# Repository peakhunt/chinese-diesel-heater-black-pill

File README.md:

# chinese-diesel-heater-black-pill
stm32f4 based chinese diesel heater

# again Dangerous!
I'm not interested in adding any safety features as of now!

# a little documentation
to be done

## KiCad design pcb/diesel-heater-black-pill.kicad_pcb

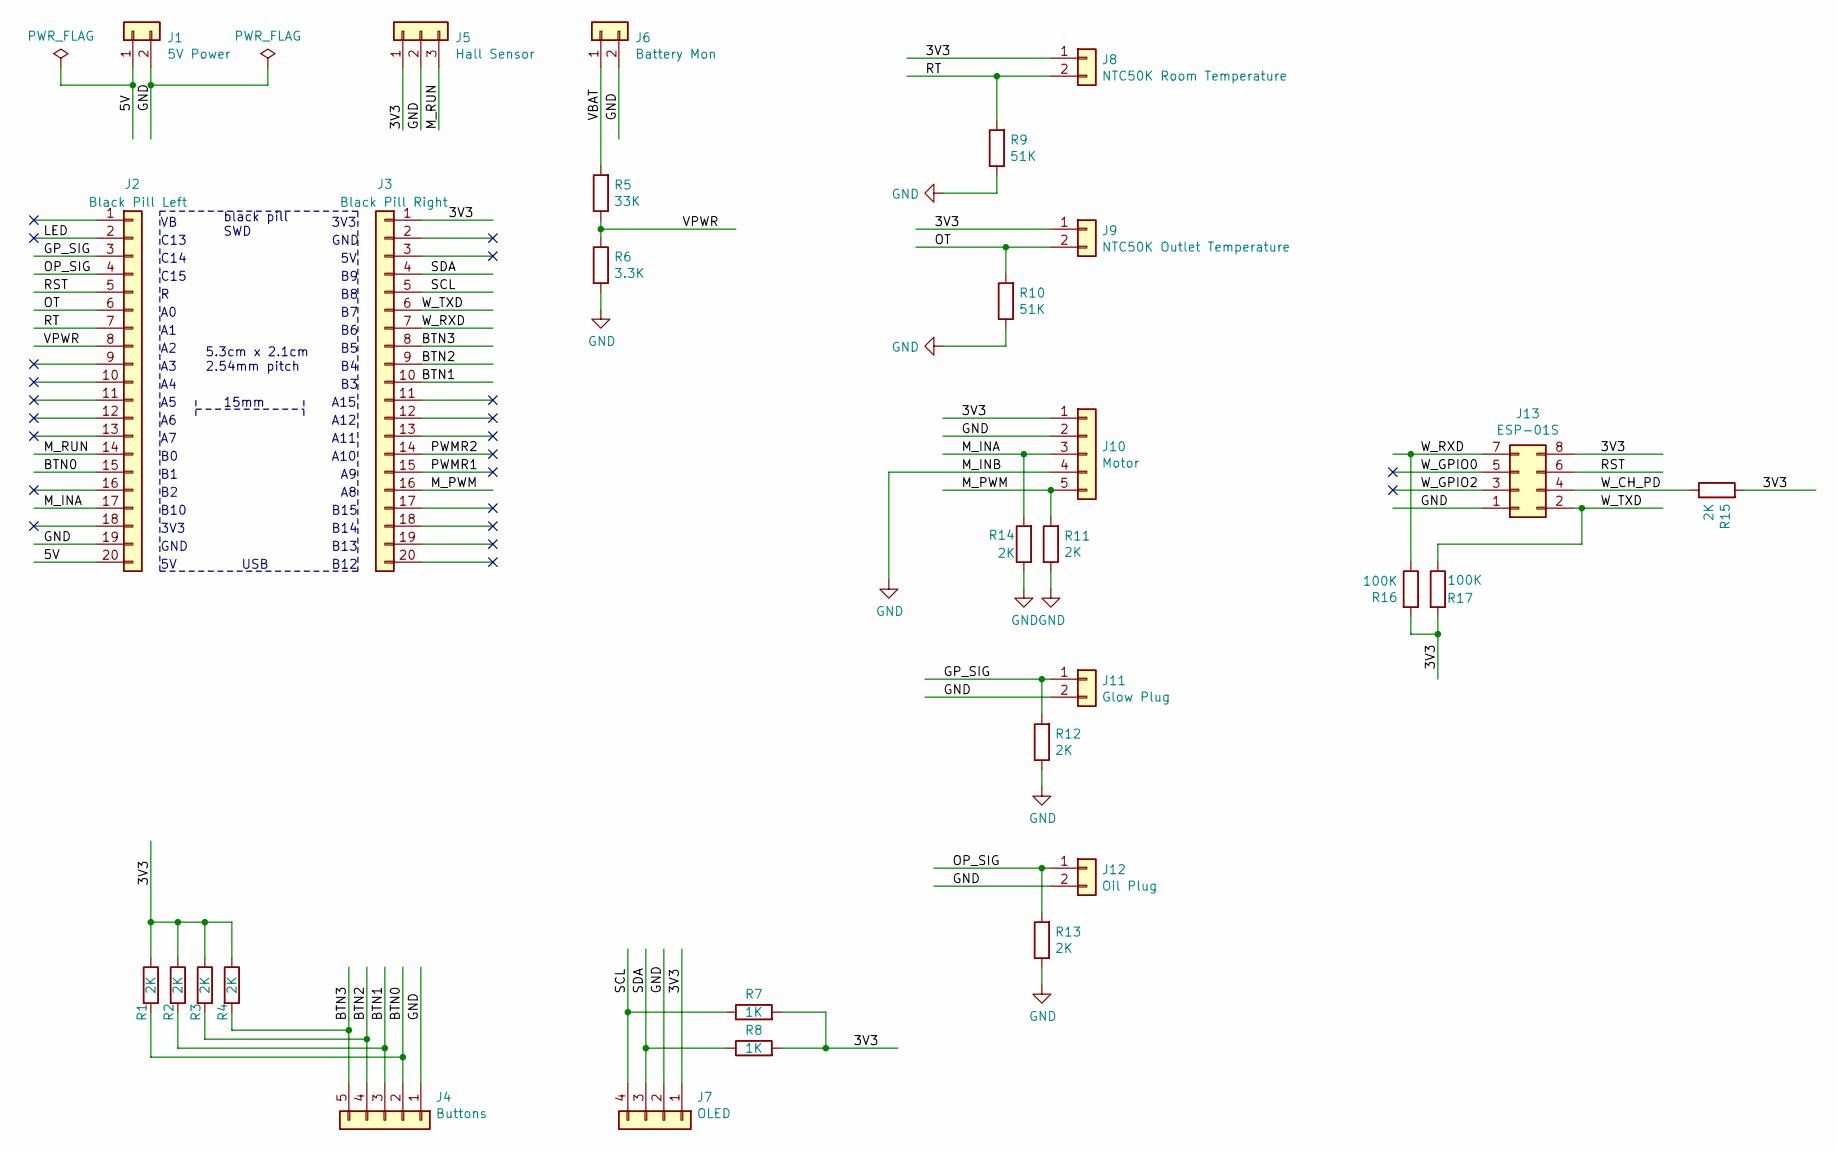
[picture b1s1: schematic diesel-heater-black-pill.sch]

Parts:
J1: 5V Power; JST_XH_B2B-XH-A_1x02_P2.50mm_Vertical
J2: Black Pill Left; PinSocket_1x20_P2.54mm_Vertical
J3: Black Pill Right; PinSocket_1x20_P2.54mm_Vertical
J4: Buttons; JST_XH_B5B-XH-A_1x05_P2.50mm_Vertical
J5: Hall Sensor; JST_XH_B3B-XH-A_1x03_P2.50mm_Vertical
J6: Battery Mon; JST_XH_B2B-XH-A_1x02_P2.50mm_Vertical
J7: OLED; JST_XH_B4B-XH-A_1x04_P2.50mm_Vertical
J8: NTC50K Room Temperature; JST_XH_B2B-XH-A_1x02_P2.50mm_Vertical
J9: NTC50K Outlet Temperature; JST_XH_B2B-XH-A_1x02_P2.50mm_Vertical
J10: Motor; JST_XH_B5B-XH-A_1x05_P2.50mm_Vertical
J11: Glow Plug; JST_XH_B2B-XH-A_1x02_P2.50mm_Vertical
J12: Oil Plug; JST_XH_B2B-XH-A_1x02_P2.50mm_Vertical
J13: ESP-01S; PinSocket_2x04_P2.54mm_Vertical
R1, R2, R3, R4, R11, R12, R13, R14, R15: 2K; R_0603_1608Metric_Pad0.98x0.95mm_HandSolder
R5: 33K; R_0603_1608Metric_Pad0.98x0.95mm_HandSolder
R6: 3.3K; R_0603_1608Metric_Pad0.98x0.95mm_HandSolder
R7, R8: 1K; R_0603_1608Metric_Pad0.98x0.95mm_HandSolder
R9, R10: 51K; R_0603_1608Metric_Pad0.98x0.95mm_HandSolder
R16, R17: 100K; R_0603_1608Metric_Pad0.98x0.95mm_HandSolder

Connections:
/3V3: J3.1, J5.1, J7.1, J8.1, J9.1, J10.1, J13.8, R1.1, R2.1, R3.1, R4.1, R7.2, R8.2, R15.2, R16.2, R17.2
/5V: J1.1, J2.20
/BTN0: J2.15, J4.2, R1.2
/BTN1: J3.10, J4.3, R2.2
/BTN2: J3.9, J4.4, R3.2
/BTN3: J3.8, J4.5, R4.2
/GP_SIG: J2.3, J11.1, R12.2
/LED: J2.2
/M_INA: J2.17, J10.3, R14.2
/M_PWM: J3.16, J10.5, R11.2
/M_RUN: J2.14, J5.3
/OP_SIG: J2.4, J12.1, R13.2
/OT: J2.6, J9.2, R10.2
/PWMR1: J3.15
/PWMR2: J3.14
/RST: J2.5, J13.6
/RT: J2.7, J8.2, R9.2
/SCL: J3.5, J7.4, R7.1
/SDA: J3.4, J7.3, R8.1
/VBAT: J6.1, R5.2
/VPWR: J2.8, R5.1, R6.1
/W_CH_PD: J13.4, R15.1
/W_GPIO0: J13.5
/W_GPIO2: J13.3
/W_RXD: J3.7, J13.7, R16.1
/W_TXD: J3.6, J13.2, R17.1
GND: J1.2, J2.19, J4.1, J5.2, J6.2, J7.2, J10.2, J10.4, J11.2, J12.2, J13.1, R6.2, R9.1, R10.1, R11.1, R12.1, R13.1, R14.1

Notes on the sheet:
black pill SWD
USB
C13
C14
C15
B10
3V3
GND
A15
A12
A11
A10
B15
B14
B13
B12
5.3cm x 2.1cm 2.54mm pitch
15mm

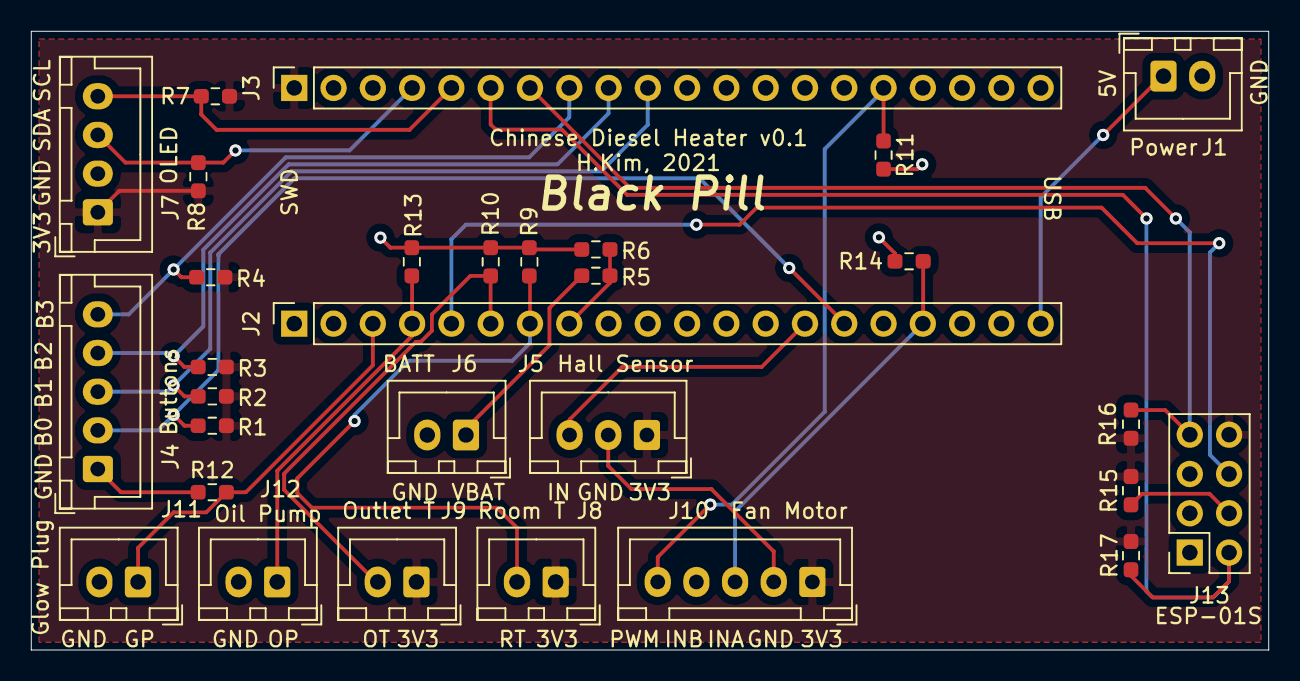
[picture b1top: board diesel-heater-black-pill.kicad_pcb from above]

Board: 2 copper layers, 80.0 x 40.0 mm, 30 parts (0 on the bottom side), 22 nets.

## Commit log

2021-02-17 first import
2021-02-17 Create LICENSE
2021-02-18 working on OLED display
2021-02-19 oled display related functions. changed gpio input pins as well
2021-02-19 added isnan guard condition to ntc50k calculation
2021-02-19 added version
2021-02-19 version test
2021-02-19 version
2021-02-19 cleanup
2021-02-19 moved common code out to utilities.h
2021-02-19 more code cleanup to use stdio for floating point printf
2021-02-19 indentation cleanup
2021-02-19 code cleanup and some comment fix
2021-02-19 more code cleanup
2021-02-22 added motor driver enable/disable signal. added ntc50k room temperature
2021-02-22 adding kicad pcb
2021-02-22 that 2fa password hell test
2021-02-23 changed pcb to add esp-01
2021-02-23 fixed ntc50k for room temperature bug
2021-02-23 minor pcb modification
2021-02-23 changed dimension from 15mm to 15.24mm
2021-02-23 fixed bug of using led pin pc13 as motor INA. added PB10 as gpio output
2021-02-23 changed to use PB10 for motor INA
2021-02-24 changed main power batter voltage divider from 6.3K to 33K
2021-02-25 added room temperature to display
2021-02-25 fixed unconnected pcb bug. kicad is weird after upgrading
2021-03-25 fixed missing voltage range in flash erase
2021-05-13 adding esp8266 web front end
